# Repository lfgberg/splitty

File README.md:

# splitty
pain27 esque ortho split

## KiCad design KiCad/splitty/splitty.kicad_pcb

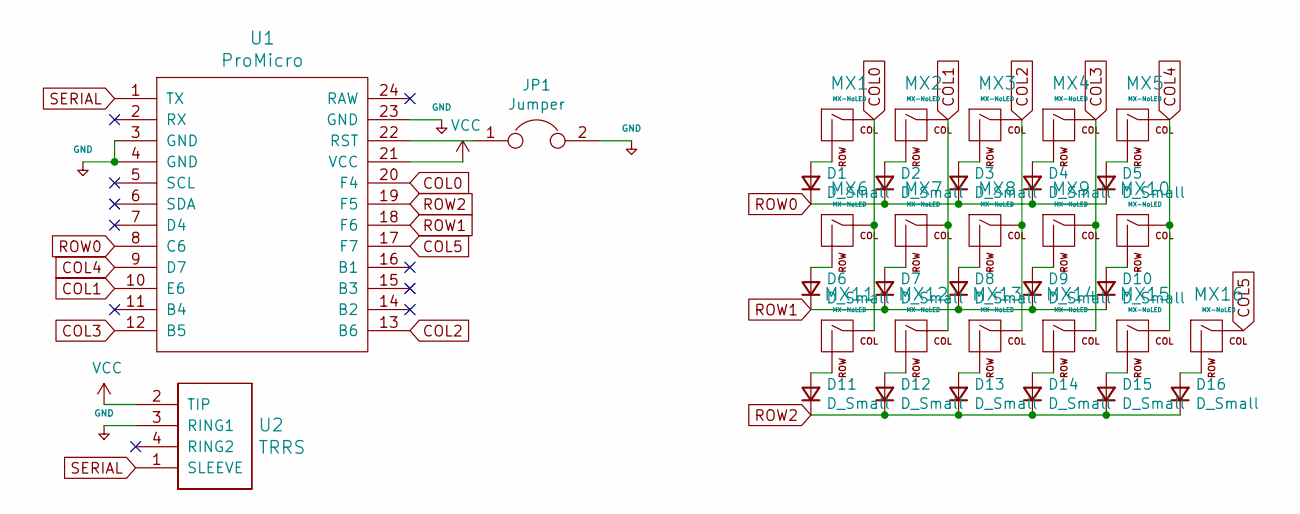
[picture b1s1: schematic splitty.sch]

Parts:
D1, D2, D3, D4, D5, D6, D7, D8, D9, D10, D11, D12, D13, D14, D15, D16: D_Small; Diode-dual
JP1: Jumper; splitty-reset-jumper
MX1, MX2, MX3, MX4, MX5, MX6, MX7, MX8, MX9, MX10, MX11, MX12, MX13, MX14, MX15, MX16: MX-NoLED; reversible-mx-alps-choc
U1: ProMicro; splitty-pro-micro
U2: TRRS; TRRS_JACK_MJ4PP9

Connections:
+5V: JP1.2, U1.3 (GND), U1.4 (GND), U1.23 (GND), U2.3 (RING1)
COL0: MX1.1 (COL), MX6.1 (COL), MX11.1 (COL), U1.20 (F4)
COL1: MX2.1 (COL), MX7.1 (COL), MX12.1 (COL), U1.10 (E6)
COL2: MX3.1 (COL), MX8.1 (COL), MX13.1 (COL), U1.13 (B6)
COL3: MX4.1 (COL), MX9.1 (COL), MX14.1 (COL), U1.12 (B5)
COL4: MX5.1 (COL), MX10.1 (COL), MX15.1 (COL), U1.9 (D7)
COL5: MX16.1 (COL), U1.17 (F7)
unnamed: D1.2 (A), MX1.2 (ROW)
unnamed: D2.2 (A), MX2.2 (ROW)
unnamed: D3.2 (A), MX3.2 (ROW)
unnamed: D4.2 (A), MX4.2 (ROW)
unnamed: D5.2 (A), MX5.2 (ROW)
unnamed: D6.2 (A), MX6.2 (ROW)
unnamed: D7.2 (A), MX7.2 (ROW)
unnamed: D8.2 (A), MX8.2 (ROW)
unnamed: D9.2 (A), MX9.2 (ROW)
unnamed: D10.2 (A), MX10.2 (ROW)
unnamed: D11.2 (A), MX11.2 (ROW)
unnamed: D12.2 (A), MX12.2 (ROW)
unnamed: D13.2 (A), MX13.2 (ROW)
unnamed: D14.2 (A), MX14.2 (ROW)
unnamed: D15.2 (A), MX15.2 (ROW)
unnamed: D16.2 (A), MX16.2 (ROW)
unnamed: JP1.1, U1.22 (RST)
ROW0: D1.1 (K), D2.1 (K), D3.1 (K), D4.1 (K), D5.1 (K), U1.8 (C6)
ROW1: D6.1 (K), D7.1 (K), D8.1 (K), D9.1 (K), D10.1 (K), U1.18 (F6)
ROW2: D11.1 (K), D12.1 (K), D13.1 (K), D14.1 (K), D15.1 (K), D16.1 (K), U1.19 (F5)
SERIAL: U1.1 (TX), U2.1 (SLEEVE)
VCC: U1.21 (VCC), U2.2 (TIP)

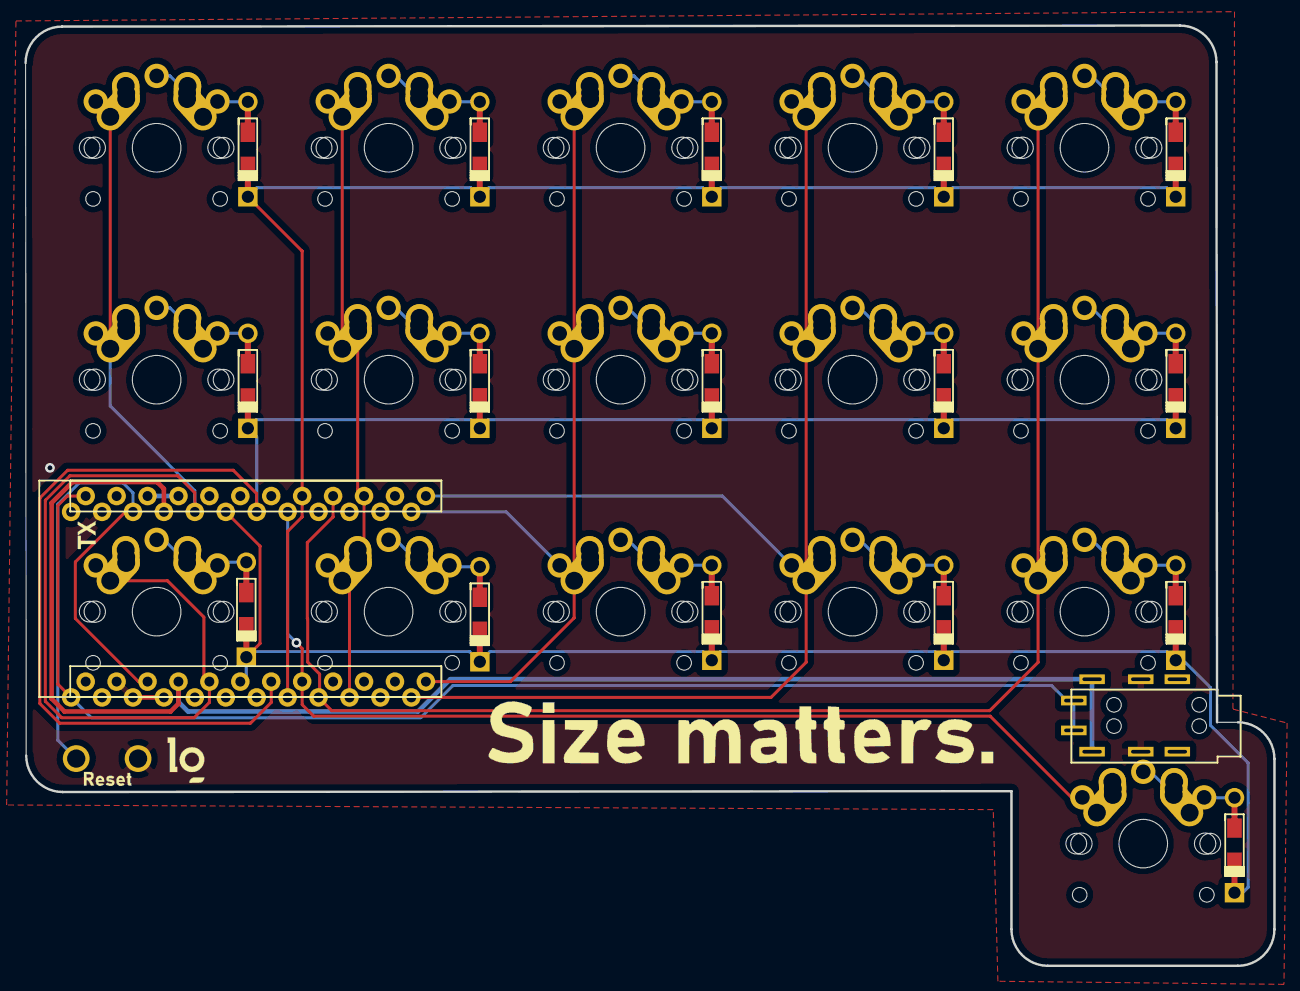
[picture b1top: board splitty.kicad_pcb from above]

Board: 2 copper layers, 102.6 x 77.2 mm, 35 parts (0 on the bottom side), 29 nets.

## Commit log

2020-11-18 finished rev1
2020-11-25 various fixes and changes
2020-12-23 changed some shit i forget
2021-04-05 .
    .
